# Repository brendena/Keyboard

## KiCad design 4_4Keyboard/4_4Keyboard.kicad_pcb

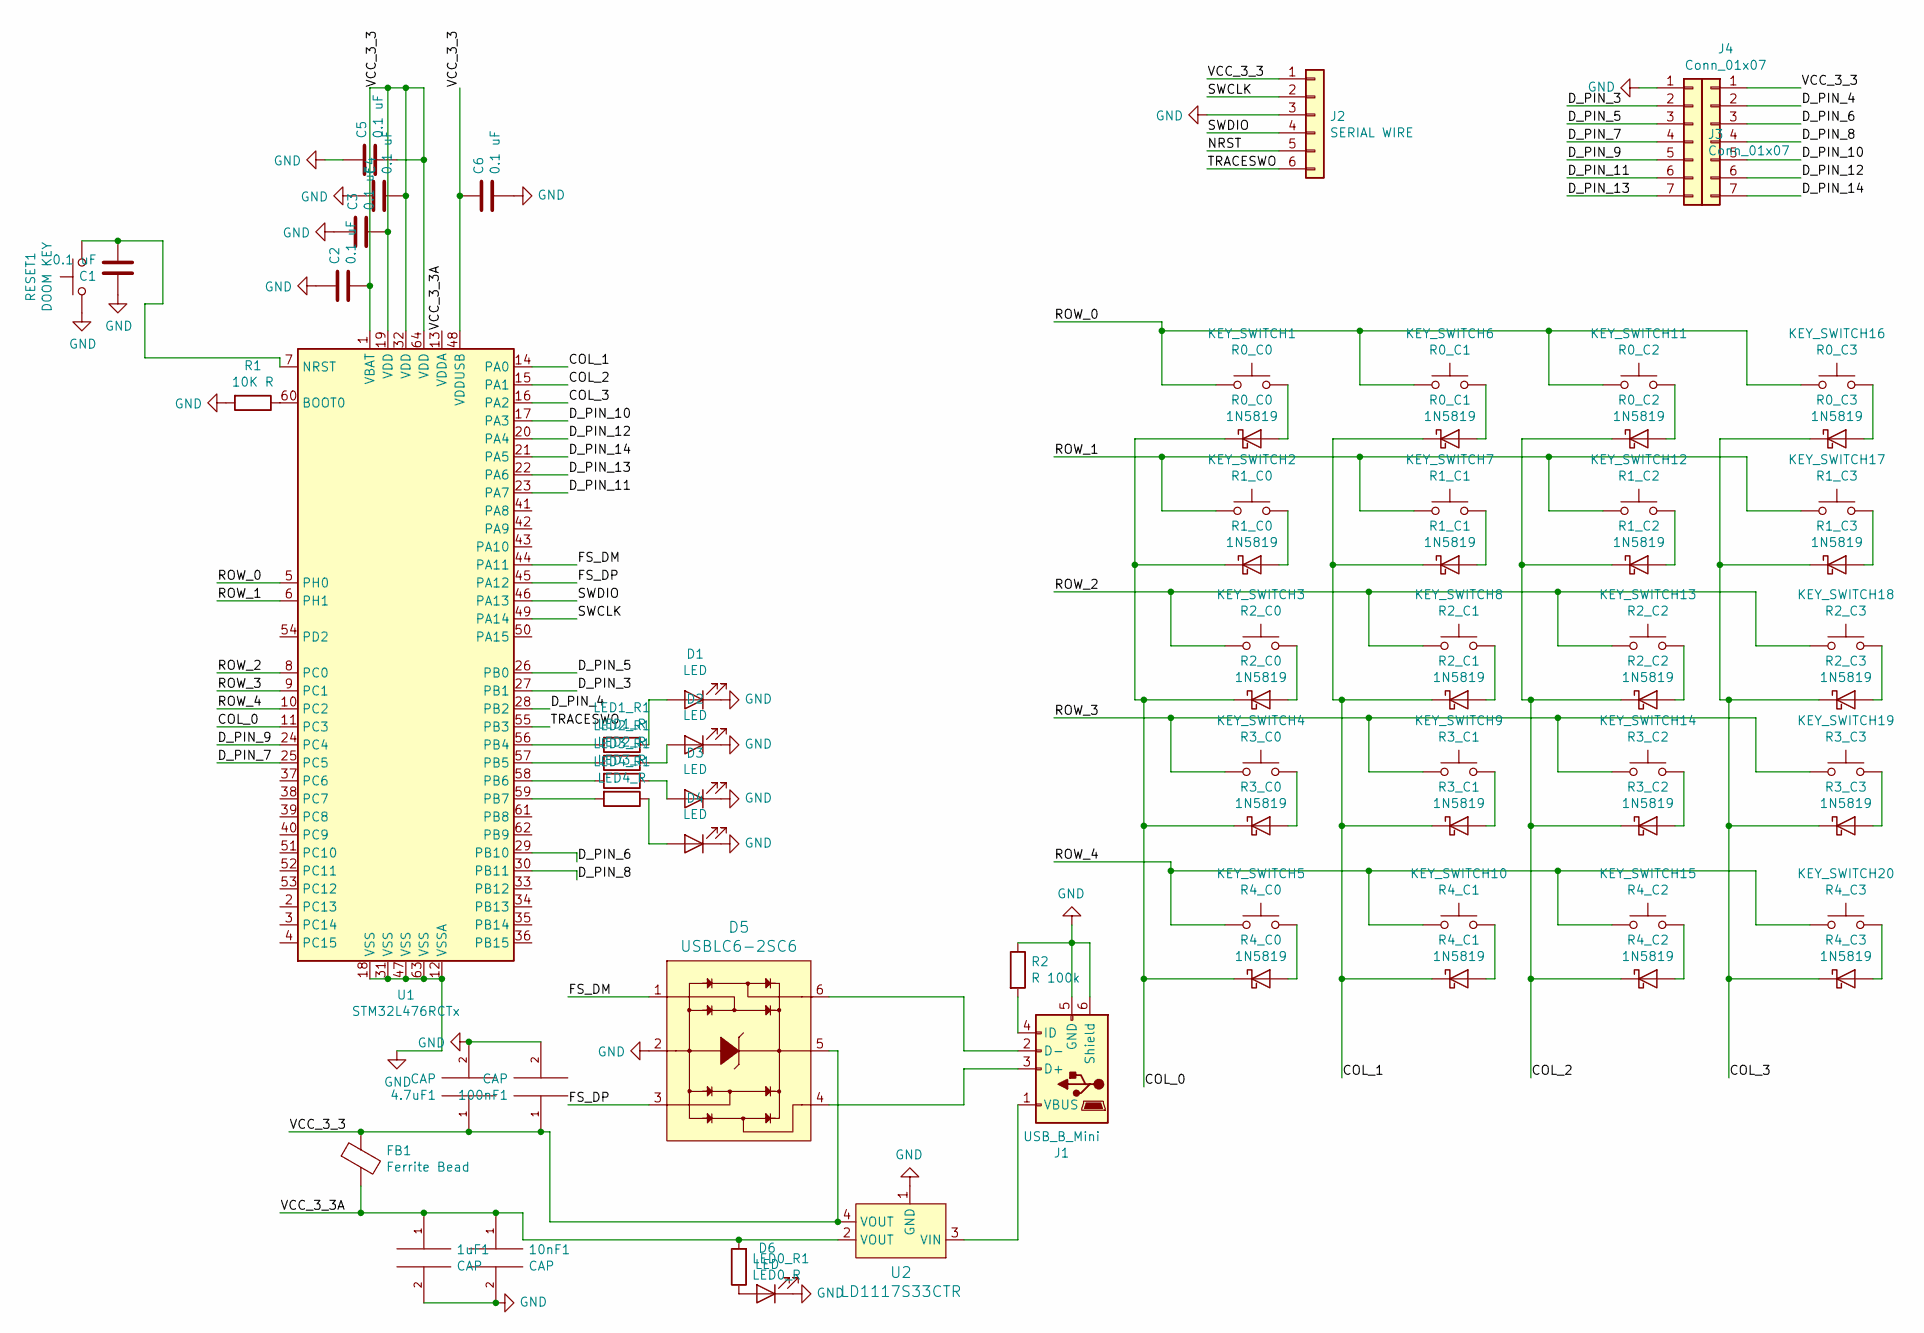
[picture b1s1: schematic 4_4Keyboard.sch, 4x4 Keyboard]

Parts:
1uF1, 4.7uF1, 10nF1, 100nF1: CAP; C_0603_1608Metric
C1, C2, C3, C4, C5, C6: 0.1 uF; C_0603_1608Metric
D1, D2, D3, D4, D6: LED; LED_D5.0mm
D5: USBLC6-2SC6; SOT23-6L; MPN USBLC6-2SC6; Digi-Key_PN 497-5235-1-ND
FB1: Ferrite Bead; L_0603_1608Metric
J1: USB_B_Mini; USB_Mini-B_Lumberg_2486_01_Horizontal
J2: SERIAL WIRE; PinHeader_1x06_P2.54mm_Vertical
J3, J4: Conn_01x07; PinHeader_1x07_P2.54mm_Vertical
KEY_SWITCH1: R0_C0; SW_Cherry_MX_1.00u_PCB
KEY_SWITCH2: R1_C0; SW_Cherry_MX_1.00u_PCB
KEY_SWITCH3: R2_C0; SW_Cherry_MX_1.00u_PCB
KEY_SWITCH4: R3_C0; SW_Cherry_MX_1.00u_PCB
KEY_SWITCH5: R4_C0; SW_Cherry_MX_1.00u_PCB
KEY_SWITCH6: R0_C1; SW_Cherry_MX_1.00u_PCB
KEY_SWITCH7: R1_C1; SW_Cherry_MX_1.00u_PCB
KEY_SWITCH8: R2_C1; SW_Cherry_MX_1.00u_PCB
KEY_SWITCH9: R3_C1; SW_Cherry_MX_1.00u_PCB
KEY_SWITCH10: R4_C1; SW_Cherry_MX_1.00u_PCB
KEY_SWITCH11: R0_C2; SW_Cherry_MX_1.00u_PCB
KEY_SWITCH12: R1_C2; SW_Cherry_MX_1.00u_PCB
KEY_SWITCH13: R2_C2; SW_Cherry_MX_1.00u_PCB
KEY_SWITCH14: R3_C2; SW_Cherry_MX_1.00u_PCB
KEY_SWITCH15: R4_C2; SW_Cherry_MX_1.00u_PCB
KEY_SWITCH16: R0_C3; SW_Cherry_MX_1.00u_PCB
KEY_SWITCH17: R1_C3; SW_Cherry_MX_1.00u_PCB
KEY_SWITCH18: R2_C3; SW_Cherry_MX_1.00u_PCB
KEY_SWITCH19: R3_C3; SW_Cherry_MX_1.00u_PCB
KEY_SWITCH20: R4_C3; SW_Cherry_MX_1.00u_PCB
LED0_R1: LED0_R; R_Axial_DIN0207_L6.3mm_D2.5mm_P7.62mm_Horizontal
LED1_R1: LED1_R; R_Axial_DIN0207_L6.3mm_D2.5mm_P7.62mm_Horizontal
LED2_R1: LED2_R; R_Axial_DIN0207_L6.3mm_D2.5mm_P7.62mm_Horizontal
LED3_R1: LED3_R; R_Axial_DIN0207_L6.3mm_D2.5mm_P7.62mm_Horizontal
LED4_R1: LED4_R; R_Axial_DIN0207_L6.3mm_D2.5mm_P7.62mm_Horizontal
R0_C0, R0_C1, R0_C2, R0_C3, R1_C0, R1_C1, R1_C2, R1_C3, R2_C0, R2_C1, R2_C2, R2_C3, R3_C0, R3_C1, R3_C2, R3_C3, R4_C0, R4_C1, R4_C2, R4_C3: 1N5819; D_DO-41_SOD81_P10.16mm_Horizontal
R1: 10K R; R_Axial_DIN0207_L6.3mm_D2.5mm_P7.62mm_Horizontal
R2: R 100k; R_Axial_DIN0207_L6.3mm_D2.5mm_P7.62mm_Horizontal
RESET1: DOOM KEY; SW_Cherry_MX_1.00u_PCB
U1: STM32L476RCTx; LQFP-64_10x10mm_P0.5mm
U2: LD1117S33CTR; SOT-223; MPN LD1117S33CTR; Digi-Key_PN 497-1241-1-ND

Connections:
/COL_0: R0_C0.1 (K), R1_C0.1 (K), R2_C0.1 (K), R3_C0.1 (K), R4_C0.1 (K), U1.11 (PC3)
/COL_1: R0_C1.1 (K), R1_C1.1 (K), R2_C1.1 (K), R3_C1.1 (K), R4_C1.1 (K), U1.14 (PA0)
/COL_2: R0_C2.1 (K), R1_C2.1 (K), R2_C2.1 (K), R3_C2.1 (K), R4_C2.1 (K), U1.15 (PA1)
/COL_3: R0_C3.1 (K), R1_C3.1 (K), R2_C3.1 (K), R3_C3.1 (K), R4_C3.1 (K), U1.16 (PA2)
/D_PIN_3: J3.2, U1.27 (PB1)
/D_PIN_4: J4.2, U1.28 (PB2)
/D_PIN_5: J3.3, U1.26 (PB0)
/D_PIN_6: J4.3, U1.29 (PB10)
/D_PIN_7: J3.4, U1.25 (PC5)
/D_PIN_8: J4.4, U1.30 (PB11)
/D_PIN_9: J3.5, U1.24 (PC4)
/D_PIN_10: J4.5, U1.17 (PA3)
/D_PIN_11: J3.6, U1.23 (PA7)
/D_PIN_12: J4.6, U1.20 (PA4)
/D_PIN_13: J3.7, U1.22 (PA6)
/D_PIN_14: J4.7, U1.21 (PA5)
/FS_DM: D5.1, U1.44 (PA11)
/FS_DP: D5.3, U1.45 (PA12)
/NRST: J2.5
/ROW_0: KEY_SWITCH1.1, KEY_SWITCH6.1, KEY_SWITCH11.1, KEY_SWITCH16.1, U1.5 (PH0)
/ROW_1: KEY_SWITCH2.1, KEY_SWITCH7.1, KEY_SWITCH12.1, KEY_SWITCH17.1, U1.6 (PH1)
/ROW_2: KEY_SWITCH3.1, KEY_SWITCH8.1, KEY_SWITCH13.1, KEY_SWITCH18.1, U1.8 (PC0)
/ROW_3: KEY_SWITCH4.1, KEY_SWITCH9.1, KEY_SWITCH14.1, KEY_SWITCH19.1, U1.9 (PC1)
/ROW_4: KEY_SWITCH5.1, KEY_SWITCH10.1, KEY_SWITCH15.1, KEY_SWITCH20.1, U1.10 (PC2)
/SWCLK: J2.2, U1.49 (PA14)
/SWDIO: J2.4, U1.46 (PA13)
/TRACESWO: J2.6, U1.55 (PB3)
/VCC_3_3: 4.7uF1.1, 100nF1.1, C2.2, C3.2, C4.2, C5.2, C6.1, D5.5, FB1.1, J2.1, J4.1, U1.1 (VBAT), U1.19 (VDD), U1.32 (VDD), U1.48 (VDDUSB), U1.64 (VDD), U2.4 (VOUT)
/VCC_3_3A: 1uF1.1, 10nF1.1, FB1.2, LED0_R1.2, U1.13 (VDDA), U2.2 (VOUT)
GND: 1uF1.2, 4.7uF1.2, 10nF1.2, 100nF1.2, C1.1, C2.1, C3.1, C4.1, C5.1, C6.2, D1.1 (K), D2.1 (K), D3.1 (K), D4.1 (K), D5.2, D6.1 (K), J1.5 (GND), J1.6 (Shield), J2.3, J3.1, R1.2, R2.1, RESET1.1, U1.12 (VSSA), U1.18 (VSS), U1.31 (VSS), U1.47 (VSS), U1.63 (VSS), U2.1 (GND)
unnamed: C1.2, RESET1.2, U1.7 (NRST)
unnamed: D1.2 (A), LED1_R1.1
unnamed: D2.2 (A), LED2_R1.1
unnamed: D3.2 (A), LED3_R1.1
unnamed: D4.2 (A), LED4_R1.1
unnamed: D5.4, J1.3 (D+)
unnamed: D5.6, J1.2 (D-)
unnamed: D6.2 (A), LED0_R1.1
unnamed: J1.1 (VBUS), U2.3 (VIN)
unnamed: J1.4 (ID), R2.2
unnamed: KEY_SWITCH1.2, R0_C0.2 (A)
unnamed: KEY_SWITCH2.2, R1_C0.2 (A)
unnamed: KEY_SWITCH3.2, R2_C0.2 (A)
unnamed: KEY_SWITCH4.2, R3_C0.2 (A)
unnamed: KEY_SWITCH5.2, R4_C0.2 (A)
unnamed: KEY_SWITCH6.2, R0_C1.2 (A)
unnamed: KEY_SWITCH7.2, R1_C1.2 (A)
unnamed: KEY_SWITCH8.2, R2_C1.2 (A)
unnamed: KEY_SWITCH9.2, R3_C1.2 (A)
unnamed: KEY_SWITCH10.2, R4_C1.2 (A)
unnamed: KEY_SWITCH11.2, R0_C2.2 (A)
unnamed: KEY_SWITCH12.2, R1_C2.2 (A)
unnamed: KEY_SWITCH13.2, R2_C2.2 (A)
unnamed: KEY_SWITCH14.2, R3_C2.2 (A)
unnamed: KEY_SWITCH15.2, R4_C2.2 (A)
unnamed: KEY_SWITCH16.2, R0_C3.2 (A)
unnamed: KEY_SWITCH17.2, R1_C3.2 (A)
unnamed: KEY_SWITCH18.2, R2_C3.2 (A)
unnamed: KEY_SWITCH19.2, R3_C3.2 (A)
unnamed: KEY_SWITCH20.2, R4_C3.2 (A)
unnamed: LED1_R1.2, U1.56 (PB4)
unnamed: LED2_R1.2, U1.57 (PB5)
unnamed: LED3_R1.2, U1.58 (PB6)
unnamed: LED4_R1.2, U1.59 (PB7)
unnamed: R1.1, U1.60 (BOOT0)

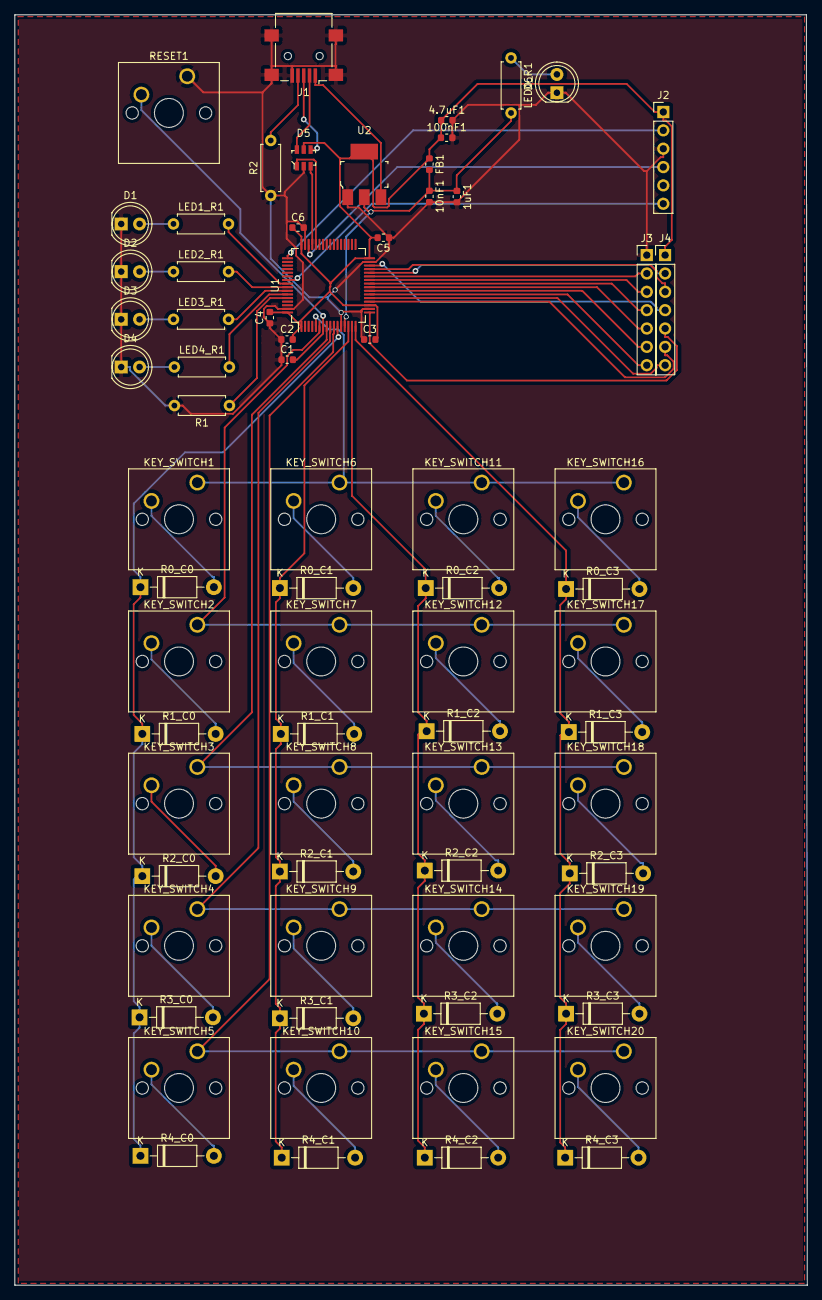
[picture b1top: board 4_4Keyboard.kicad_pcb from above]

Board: 2 copper layers, 109.7 x 175.9 mm, 71 parts (0 on the bottom side), 64 nets.

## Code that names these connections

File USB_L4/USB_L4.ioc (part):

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Mcu.Name=STM32L476R(C-E-G)Tx
Mcu.Package=LQFP64
Mcu.UserName=STM32L476RCTx
PA0.GPIOParameters=GPIO_PuPd,GPIO_Label
PA0.GPIO_Label=COL_1_INPUT
PA0.GPIO_PuPd=GPIO_PULLDOWN
PA0.Signal=GPIO_Input
PA1.GPIOParameters=GPIO_PuPd,GPIO_Label
PA1.GPIO_Label=COL_2_INPUT
PA1.GPIO_PuPd=GPIO_PULLDOWN
PA1.Signal=GPIO_Input
PA11.Mode=Device_Only
PA11.Signal=USB_OTG_FS_DM
PA12.Mode=Device_Only
PA12.Signal=USB_OTG_FS_DP
PA13\ (JTMS-SWDIO).Mode=Trace_Asynchronous_SW
PA13\ (JTMS-SWDIO).Signal=SYS_JTMS-SWDIO
PA14\ (JTCK-SWCLK).Mode=Trace_Asynchronous_SW
PA14\ (JTCK-SWCLK).Signal=SYS_JTCK-SWCLK
PA2.GPIOParameters=GPIO_PuPd,GPIO_Label
PA2.GPIO_Label=COL_3_INPUT
PA2.GPIO_PuPd=GPIO_PULLDOWN
PA2.Signal=GPIO_Input
PA6.Mode=CTS_RTS
PA6.Signal=USART3_CTS
PB1.Mode=CTS_RTS
PB1.Signal=USART3_RTS
PB3\ (JTDO-TRACESWO).Mode=Trace_Asynchronous_SW
PB3\ (JTDO-TRACESWO).Signal=SYS_JTDO-SWO
PB4\ (NJTRST).GPIOParameters=PinState,GPIO_Label
PB4\ (NJTRST).GPIO_Label=ERROR_LED
PB4\ (NJTRST).PinState=GPIO_PIN_RESET
PB4\ (NJTRST).Signal=GPIO_Output
PB5.GPIOParameters=PinState,GPIO_Label
PB5.GPIO_Label=MODE_1
PB5.PinState=GPIO_PIN_RESET
PB5.Signal=GPIO_Output
PB6.GPIOParameters=PinState,GPIO_Label
PB6.GPIO_Label=MODE_2
PB6.PinState=GPIO_PIN_RESET
PB6.Signal=GPIO_Output
PB7.GPIOParameters=PinState,GPIO_Label
PB7.GPIO_Label=MODE_3
PB7.PinState=GPIO_PIN_RESET
PB7.Signal=GPIO_Output
PC0.GPIOParameters=GPIO_Speed,PinState,GPIO_Label,GPIO_ModeDefaultOutputPP
PC0.GPIO_Label=ROW_2_OUTPUT
PC0.GPIO_ModeDefaultOutputPP=GPIO_MODE_OUTPUT_PP
PC0.GPIO_Speed=GPIO_SPEED_FREQ_HIGH
PC0.PinState=GPIO_PIN_RESET
PC0.Signal=GPIO_Output
PC1.GPIOParameters=GPIO_Speed,GPIO_Label
PC1.GPIO_Label=ROW_3_OUTPUT
PC1.GPIO_Speed=GPIO_SPEED_FREQ_HIGH
PC1.Signal=GPIO_Output
PC2.GPIOParameters=GPIO_Speed,GPIO_Label
PC2.GPIO_Label=ROW_4_OUTPUT
PC2.GPIO_Speed=GPIO_SPEED_FREQ_HIGH
PC2.Signal=GPIO_Output
PC3.GPIOParameters=GPIO_PuPd,GPIO_Label
PC3.GPIO_Label=COL_0_INPUT
PC3.GPIO_PuPd=GPIO_PULLDOWN
PC3.Signal=GPIO_Input
PC4.Mode=Asynchronous
PC4.Signal=USART3_TX
PC5.Mode=Asynchronous
PC5.Signal=USART3_RX
PH0-OSC_IN\ (PH0).GPIOParameters=GPIO_Speed,GPIO_Label
PH0-OSC_IN\ (PH0).GPIO_Label=ROW_0_OUTPUT
PH0-OSC_IN\ (PH0).GPIO_Speed=GPIO_SPEED_FREQ_HIGH
PH0-OSC_IN\ (PH0).Signal=GPIO_Output
PH1-OSC_OUT\ (PH1).GPIOParameters=GPIO_Speed,GPIO_Label
PH1-OSC_OUT\ (PH1).GPIO_Label=ROW_1_OUTPUT
PH1-OSC_OUT\ (PH1).GPIO_Speed=GPIO_SPEED_FREQ_HIGH
PH1-OSC_OUT\ (PH1).Signal=GPIO_Output
RCC.HSE_VALUE=8000000
RCC.SYSCLKFreq_VALUE=80000000
RCC.SYSCLKSource=RCC_SYSCLKSOURCE_PLLCLK
board=custom

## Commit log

2019-09-14 i think its done?
2019-09-14 added code
2019-09-14 Patrick Commit
2019-09-14 Board layout first push
2019-09-15 Board Design Start
2019-09-28 Trace ripup
2019-09-28 Autorouting prep
2019-09-28 Autorouting complete
2019-09-28 First Version Done
2019-10-19 Final Push
2020-11-14 added basic support for keyboard hex to usb
